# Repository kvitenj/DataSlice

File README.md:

# DataSlice

A credit card-sized computer for wireless and wired communication debugging

---

## 🔖 Overview

The project is inspired by the [M5Stack Cardputer](https://docs.m5stack.com/en/core/Cardputer%20V1.1).

The key features of the DataSlice:

- Credit card size to easily fit in any pocket
- QWERTY tactile keyboard for easy and fast command and data input
- "Large" 2.2-inch OLED monochrome LCD with 128x32 resolution. It is monochrome and has less resolution than M5Stack, but it is larger and fits nicely for text terminal data
- ESP32 module as a central processing unit capable of Bluetooth and WiFi communication
- SD card slot for Data storage
- Large and slim battery for long-term operation
- RS-232, UART, SPI, I2C I/O for wired communication debugging
- CC1101 and LoRa transceivers for wireless communication debugging

---

## 📁 Repository Contents

| File | Description |
|------|-------------|
| `DataSliceHW` | Folder containing the KiCAD project for the DataSlice PCB and Schematic |
| `images` | Folder containing the concept renders | 
| `LICENSE` | This repository license file |
| `README.md` | This file |

---

## 📬 Contributing

You may submit pull requests or fork the repo. But since it is a hobby project, I may respond with significant delays

---

## 🌸 License

Licensed under the [Flower License](./LICENSE) 🌸

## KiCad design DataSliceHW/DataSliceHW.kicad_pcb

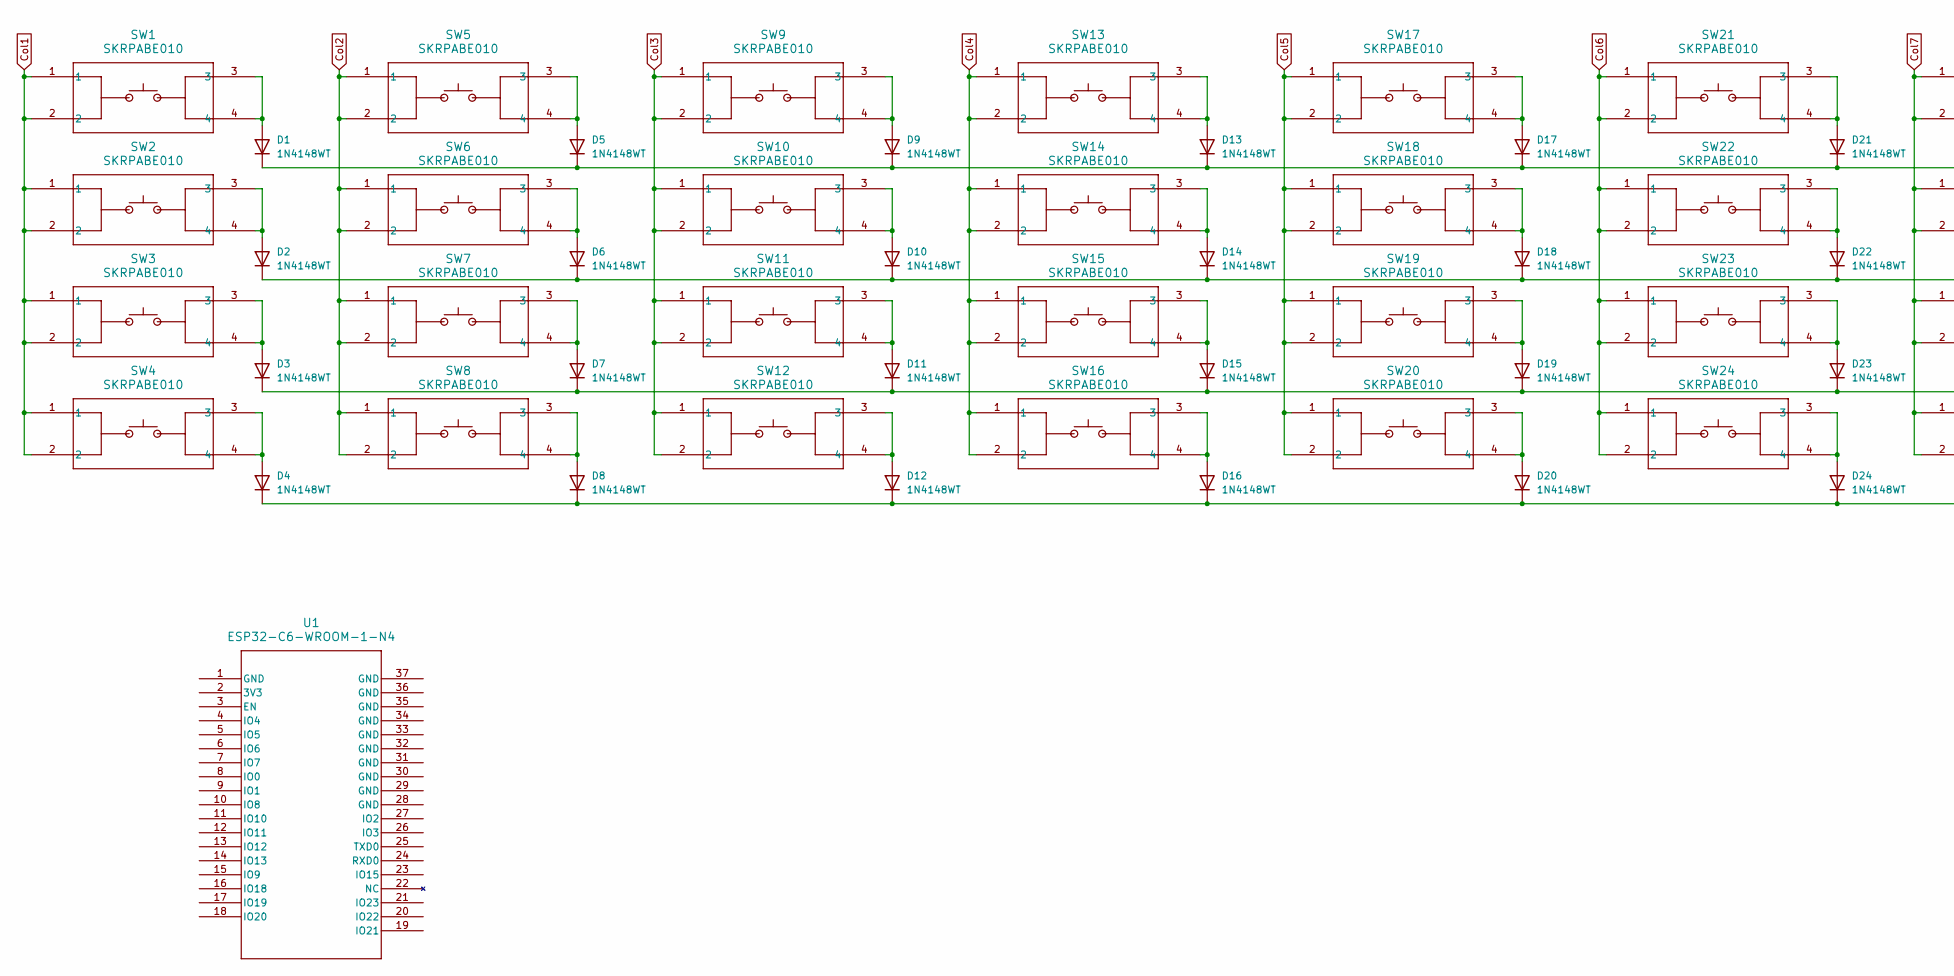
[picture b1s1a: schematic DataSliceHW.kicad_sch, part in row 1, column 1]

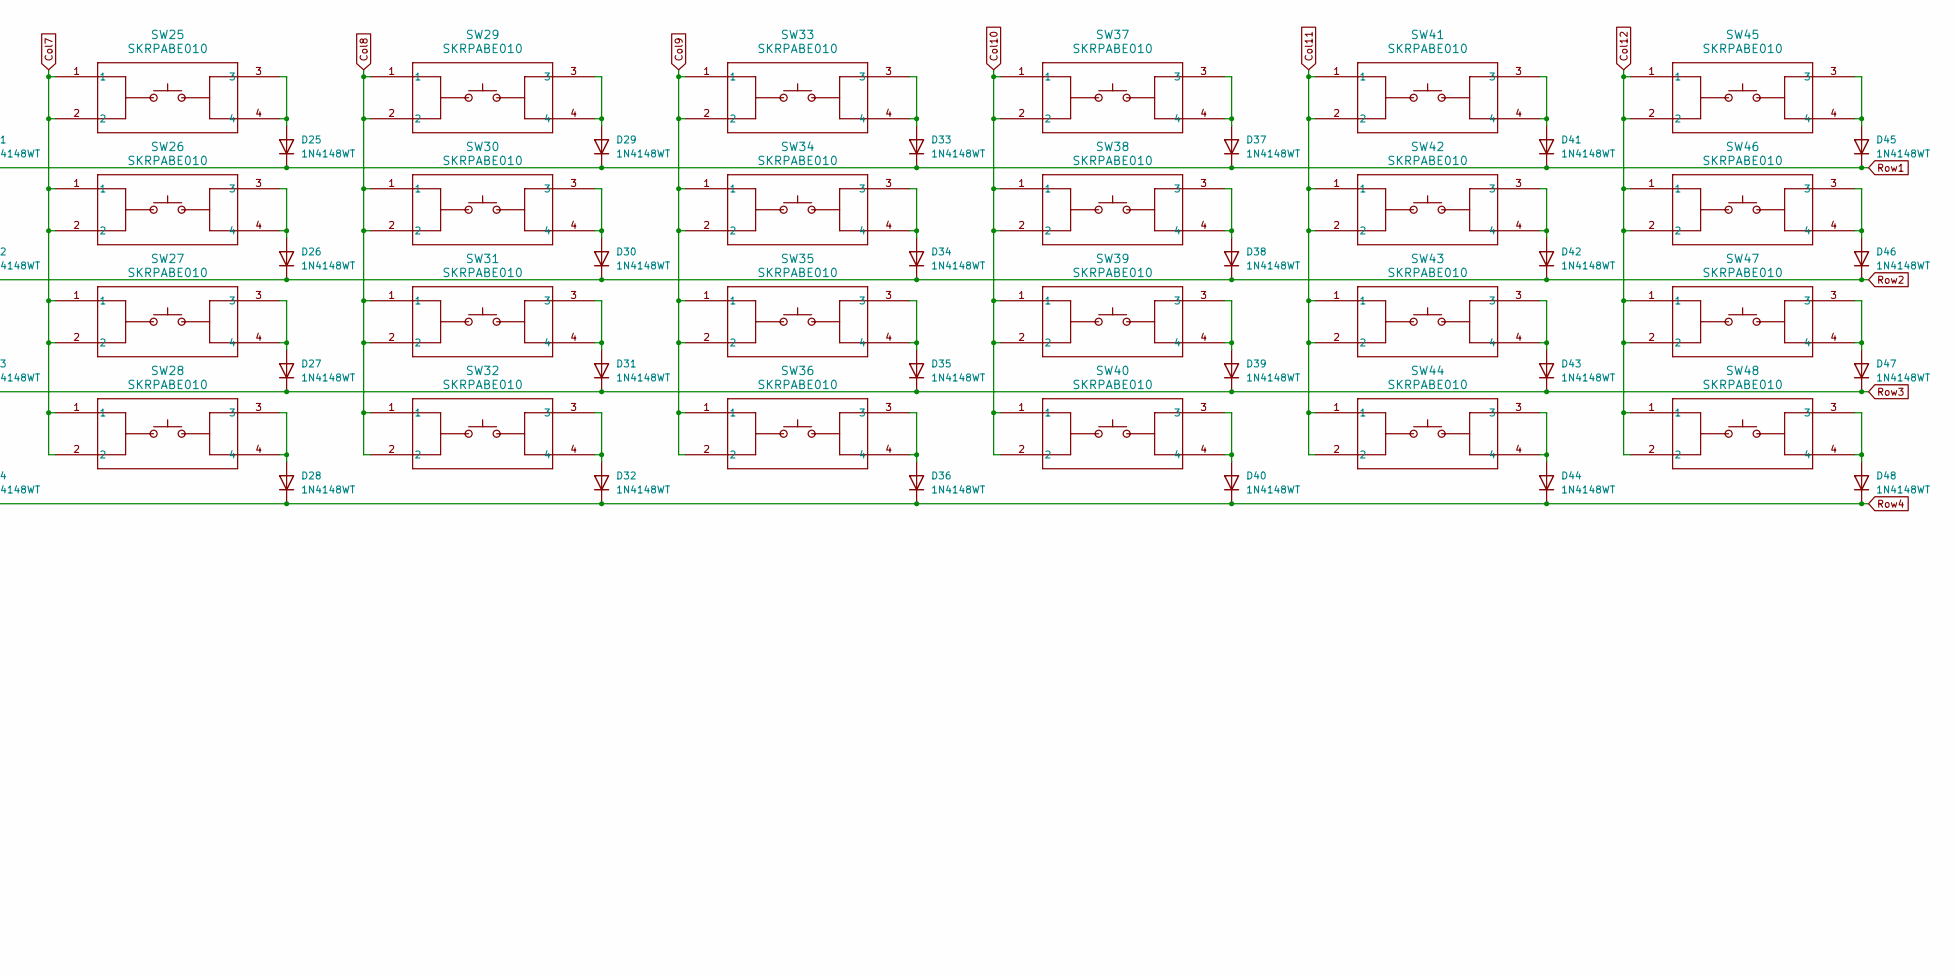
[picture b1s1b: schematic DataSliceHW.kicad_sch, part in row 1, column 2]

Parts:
D1, D2, D3, D4, D5, D6, D7, D8, D9, D10, D11, D12, D13, D14, D15, D16, D17, D18, D19, D20, D21, D22, D23, D24, D25, D26, D27, D28, D29, D30, D31, D32, D33, D34, D35, D36, D37, D38, D39, D40, D41, D42, D43, D44, D45, D46, D47, D48: 1N4148WT; D_SOD-523
SW1, SW2, SW3, SW4, SW5, SW6, SW7, SW8, SW9, SW10, SW11, SW12, SW13, SW14, SW15, SW16, SW17, SW18, SW19, SW20, SW21, SW22, SW23, SW24, SW25, SW26, SW27, SW28, SW29, SW30, SW31, SW32, SW33, SW34, SW35, SW36, SW37, SW38, SW39, SW40, SW41, SW42, SW43, SW44, SW45, SW46, SW47, SW48: SKRPABE010; SW4_SKRPABE010_ALPS
U1: ESP32-C6-WROOM-1-N4; MOD28_ESP32-C6-WROOM-1_EXP

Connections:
Col1: SW1.1, SW1.2, SW2.1, SW2.2, SW3.1, SW3.2, SW4.1, SW4.2
Col2: SW5.1, SW5.2, SW6.1, SW6.2, SW7.1, SW7.2, SW8.1, SW8.2
Col3: SW9.1, SW9.2, SW10.1, SW10.2, SW11.1, SW11.2, SW12.1, SW12.2
Col4: SW13.1, SW13.2, SW14.1, SW14.2, SW15.1, SW15.2, SW16.1, SW16.2
Col5: SW17.1, SW17.2, SW18.1, SW18.2, SW19.1, SW19.2, SW20.1, SW20.2
Col6: SW21.1, SW21.2, SW22.1, SW22.2, SW23.1, SW23.2, SW24.1, SW24.2
Col7: SW25.1, SW25.2, SW26.1, SW26.2, SW27.1, SW27.2, SW28.1, SW28.2
Col8: SW29.1, SW29.2, SW30.1, SW30.2, SW31.1, SW31.2, SW32.1, SW32.2
Col9: SW33.1, SW33.2, SW34.1, SW34.2, SW35.1, SW35.2, SW36.1, SW36.2
Col10: SW37.1, SW37.2, SW38.1, SW38.2, SW39.1, SW39.2, SW40.1, SW40.2
Col11: SW41.1, SW41.2, SW42.1, SW42.2, SW43.1, SW43.2, SW44.1, SW44.2
Col12: SW45.1, SW45.2, SW46.1, SW46.2, SW47.1, SW47.2, SW48.1, SW48.2
unnamed: D1.2 (A), SW1.3, SW1.4
unnamed: D2.2 (A), SW2.3, SW2.4
unnamed: D3.2 (A), SW3.3, SW3.4
unnamed: D4.2 (A), SW4.3, SW4.4
unnamed: D5.2 (A), SW5.3, SW5.4
unnamed: D6.2 (A), SW6.3, SW6.4
unnamed: D7.2 (A), SW7.3, SW7.4
unnamed: D8.2 (A), SW8.3, SW8.4
unnamed: D9.2 (A), SW9.3, SW9.4
unnamed: D10.2 (A), SW10.3, SW10.4
unnamed: D11.2 (A), SW11.3, SW11.4
unnamed: D12.2 (A), SW12.3, SW12.4
unnamed: D13.2 (A), SW13.3, SW13.4
unnamed: D14.2 (A), SW14.3, SW14.4
unnamed: D15.2 (A), SW15.3, SW15.4
unnamed: D16.2 (A), SW16.3, SW16.4
unnamed: D17.2 (A), SW17.3, SW17.4
unnamed: D18.2 (A), SW18.3, SW18.4
unnamed: D19.2 (A), SW19.3, SW19.4
unnamed: D20.2 (A), SW20.3, SW20.4
unnamed: D21.2 (A), SW21.3, SW21.4
unnamed: D22.2 (A), SW22.3, SW22.4
unnamed: D23.2 (A), SW23.3, SW23.4
unnamed: D24.2 (A), SW24.3, SW24.4
unnamed: D25.2 (A), SW25.3, SW25.4
unnamed: D26.2 (A), SW26.3, SW26.4
unnamed: D27.2 (A), SW27.3, SW27.4
unnamed: D28.2 (A), SW28.3, SW28.4
unnamed: D29.2 (A), SW29.3, SW29.4
unnamed: D30.2 (A), SW30.3, SW30.4
unnamed: D31.2 (A), SW31.3, SW31.4
unnamed: D32.2 (A), SW32.3, SW32.4
unnamed: D33.2 (A), SW33.3, SW33.4
unnamed: D34.2 (A), SW34.3, SW34.4
unnamed: D35.2 (A), SW35.3, SW35.4
unnamed: D36.2 (A), SW36.3, SW36.4
unnamed: D37.2 (A), SW37.3, SW37.4
unnamed: D38.2 (A), SW38.3, SW38.4
unnamed: D39.2 (A), SW39.3, SW39.4
unnamed: D40.2 (A), SW40.3, SW40.4
unnamed: D41.2 (A), SW41.3, SW41.4
unnamed: D42.2 (A), SW42.3, SW42.4
unnamed: D43.2 (A), SW43.3, SW43.4
unnamed: D44.2 (A), SW44.3, SW44.4
unnamed: D45.2 (A), SW45.3, SW45.4
unnamed: D46.2 (A), SW46.3, SW46.4
unnamed: D47.2 (A), SW47.3, SW47.4
unnamed: D48.2 (A), SW48.3, SW48.4
Row1: D1.1 (K), D5.1 (K), D9.1 (K), D13.1 (K), D17.1 (K), D21.1 (K), D25.1 (K), D29.1 (K), D33.1 (K), D37.1 (K), D41.1 (K), D45.1 (K)
Row2: D2.1 (K), D6.1 (K), D10.1 (K), D14.1 (K), D18.1 (K), D22.1 (K), D26.1 (K), D30.1 (K), D34.1 (K), D38.1 (K), D42.1 (K), D46.1 (K)
Row3: D3.1 (K), D7.1 (K), D11.1 (K), D15.1 (K), D19.1 (K), D23.1 (K), D27.1 (K), D31.1 (K), D35.1 (K), D39.1 (K), D43.1 (K), D47.1 (K)
Row4: D4.1 (K), D8.1 (K), D12.1 (K), D16.1 (K), D20.1 (K), D24.1 (K), D28.1 (K), D32.1 (K), D36.1 (K), D40.1 (K), D44.1 (K), D48.1 (K)

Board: 2 copper layers, 97 parts (0 on the bottom side), 64 nets, no tracks yet.

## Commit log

2025-07-20 Adjusted README images
2026-05-08 Update images
